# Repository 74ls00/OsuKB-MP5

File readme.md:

# Клавиатура для OSU!

Проект на базе клавиатуры v2 от noodlefighter, использованы кнопки МП9Р-1

.

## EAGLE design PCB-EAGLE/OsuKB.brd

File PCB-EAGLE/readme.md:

doc/ схема и плата в png.

OsuKB.sch OsuKB.brd плата схема и библиотека в формате eagle.

ExportGerber.cam задание экспорта в gerber/ .

SL6Import.lay6 плата импортированая в Sprint Layout 6.0 из gerber .

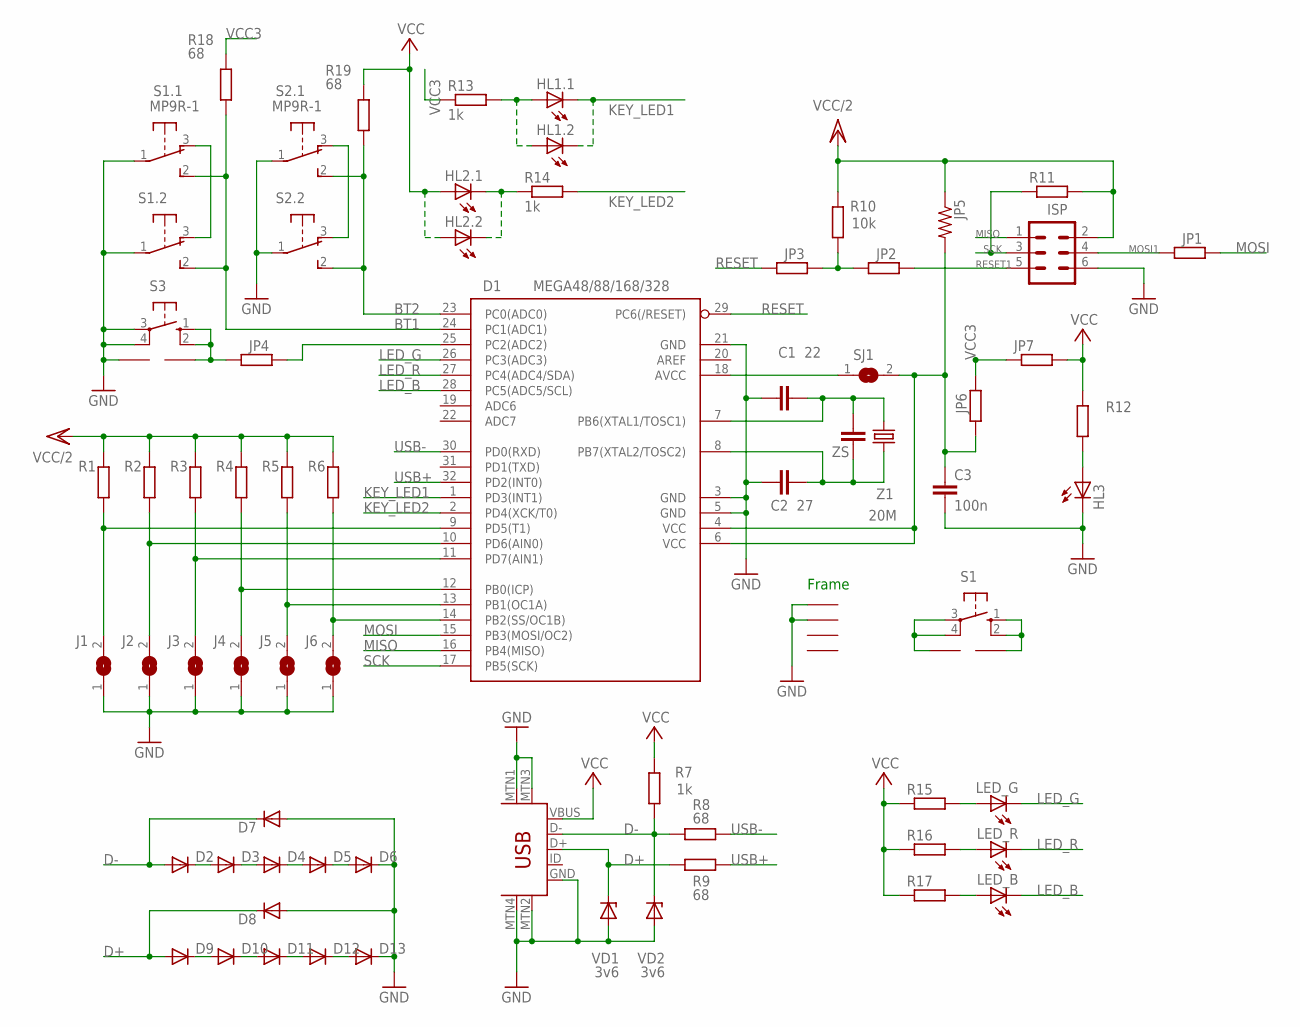
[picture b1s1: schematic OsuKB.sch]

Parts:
C1: 22; C0805
C2: 27; C0805
C3: 100n; C0805
D1: MEGA48/88/168/328; TQFP32-08
D2, D3, D4, D5, D6, D7, D8, D9, D10, D11, D12, D13: DIODE-SOD80C; SOD80C
GND: KB2
HL1.1, HL1.2, HL2.1, HL2.2: LEDSQR2X5; LED2X5
HL3: LEDSML0805; SML0805
ISP: MA03-2
J1, J2, J3, J4, J5, J6: SJ
JP1, JP2, JP3, JP4, JP6, JP7: R-EU_R1206W; R1206W
JP5: RESISTOR0805-RES; 0805
LED_B: LEDKA-3528ASYC; KA-3528ASYC
LED_G: LEDKA-3528ASYC; KA-3528ASYC
LED_R: LEDKA-3528ASYC; KA-3528ASYC
R1, R2, R3, R4, R5: R-EU_R1206W; R1206W
R6, R12, R15, R16, R17: R-EU_R0805; R0805
R7: 1k; R0805
R8, R9, R18, R19: 68; R0805
R10: 10k; R1206W
R11: R-EU_R0402; R0402
R13: 1k; R1206W
R14: 1k; 0207/12
S1: 10-XX; B3F-10XX; MPN B3F-1000
S1.1, S2.1: MP9R-1; MP5
S1.2, S2.2: MP5
S3: 10-XX; B3F-10XX
SJ1: SJ
U$1, U$6: PROGRAMMER_5.08; PROGRAMMER_KEY
VD1, VD2: 3v6; DO34Z7
X1: USB-MINIB-5PIN; USB-MINIB
Z1: 20M; HC49/S
ZS: C-EUC1812K; C1812K

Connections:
AVCC: D1.18 (AVCC), SJ1.1
BT1: D1.24 (PC1(ADC1)), R18.1, S1.1.2, S1.2.2
BT2: D1.23 (PC0(ADC0)), R19.1, S2.1.2, S2.2.2
BT3: D1.25 (PC2(ADC2)), JP4.1
D+: D8.C, D9.A, R9.1, VD1.C, X1.D+
D-: D2.A, D7.C, R7.1, R8.1, VD2.C, X1.D-
GND: C1.1, C2.1, C3.2, D1.3 (GND), D1.5 (GND), D1.21 (GND), D6.C, D7.A, D8.A, D13.C, GND.P$1 (1), GND.P$2 (2), HL3.C, ISP.6, J1.1, J2.1, J3.1, J4.1, J5.1, J6.1, S1.1.1, S1.2.1, S2.1.1, S2.2.1, S3.3, S3.4 (P1), U$6.P$1, VD1.A, VD2.A, X1.GND, X1.MTN1 (MTN2), X1.MTN2 (MTN3), X1.MTN3 (MTN1), X1.MTN4
KEY_LED1: D1.1 (PD3(INT1)), HL1.1.K (C), HL1.2.K (C)
KEY_LED2: D1.2 (PD4(XCK/T0)), R14.2
KEY_LED2.1: HL2.1.K (C), HL2.2.K (C), R14.1
LED_B: D1.28 (PC5(ADC5/SCL)), LED_B.C
LED_G: D1.26 (PC3(ADC3)), LED_G.C
LED_R: D1.27 (PC4(ADC4/SDA)), LED_R.C
MISO: D1.16 (PB4(MISO)), ISP.1
MOSI: D1.15 (PB3(MOSI/OC2)), JP1.1
MOSI1: ISP.4, JP1.2
unnamed: LED_G.A, R15.2
unnamed: D2.C, D3.A
unnamed: D3.C, D4.A
unnamed: D1.13 (PB1(OC1A)), J5.2, R5.1
unnamed: D1.14 (PB2(SS/OC1B)), J6.2, R6.1
unnamed: D1.10 (PD6(AIN0)), J2.2, R2.1
unnamed: D1.9 (PD5(T1)), J1.2, R1.1
unnamed: S1.1.3, S1.2.3
unnamed: D1.11 (PD7(AIN1)), J3.2, R3.1
unnamed: D1.12 (PB0(ICP)), J4.2, R4.1
unnamed: HL1.1.A, HL1.2.A, R13.2
unnamed: C1.2, D1.7 (PB6(XTAL1/TOSC1)), Z1.1, ZS.1
unnamed: C2.2, D1.8 (PB7(XTAL2/TOSC2)), Z1.2, ZS.2
unnamed: D4.C, D5.A
unnamed: HL3.A, R12.1
unnamed: S2.1.3, S2.2.3
unnamed: LED_R.A, R16.2
unnamed: LED_B.A, R17.2
unnamed: D5.C, D6.A
unnamed: D9.C, D10.A
unnamed: JP2.2, JP3.1, R10.1
unnamed: D10.C, D11.A
unnamed: D11.C, D12.A
unnamed: D12.C, D13.A
unnamed: C3.1, D1.4 (VCC), D1.6 (VCC), JP5.2, JP6.2, SJ1.2
unnamed: S1.3, S1.4 (P1), U$1.P$1
unnamed: S1.1 (S), S1.2 (S1), U$1.P$2
RESET: D1.29 (PC6(/RESET)), JP3.2
RESET1: ISP.5, JP2.1
S3: JP4.2, S3.1 (S), S3.2 (S1), U$6.P$2
SCK: D1.17 (PB5(SCK)), ISP.3, R11.1
USB+: D1.32 (PD2(INT0)), R9.2
USB-: D1.30 (PD0(RXD)), R8.2
VCC: HL2.1.A, HL2.2.A, JP7.2, R7.2, R12.2, R15.1, R16.1, R17.1, R19.2, X1.VBUS
VCC3: JP6.1, JP7.1, R13.1, R18.2
VCC/2: ISP.2, JP5.1, R1.2, R2.2, R3.2, R4.2, R5.2, R6.2, R10.2, R11.2

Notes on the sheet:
Frame

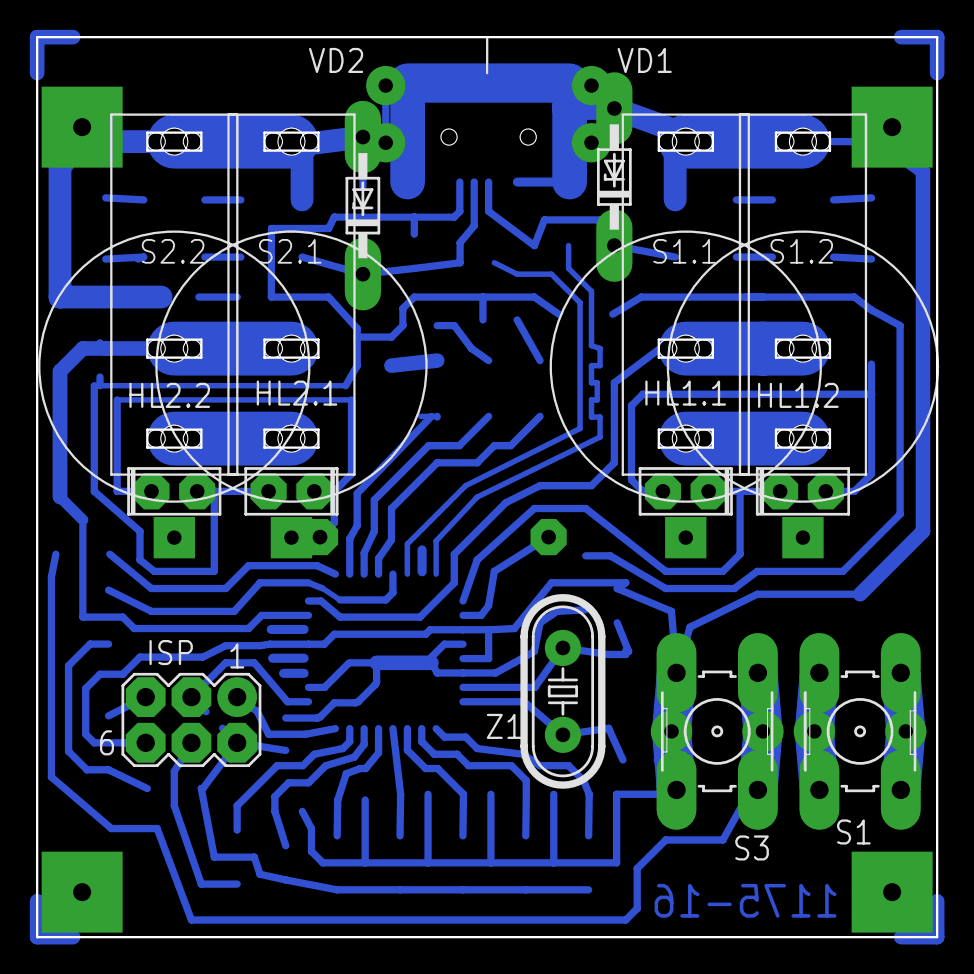
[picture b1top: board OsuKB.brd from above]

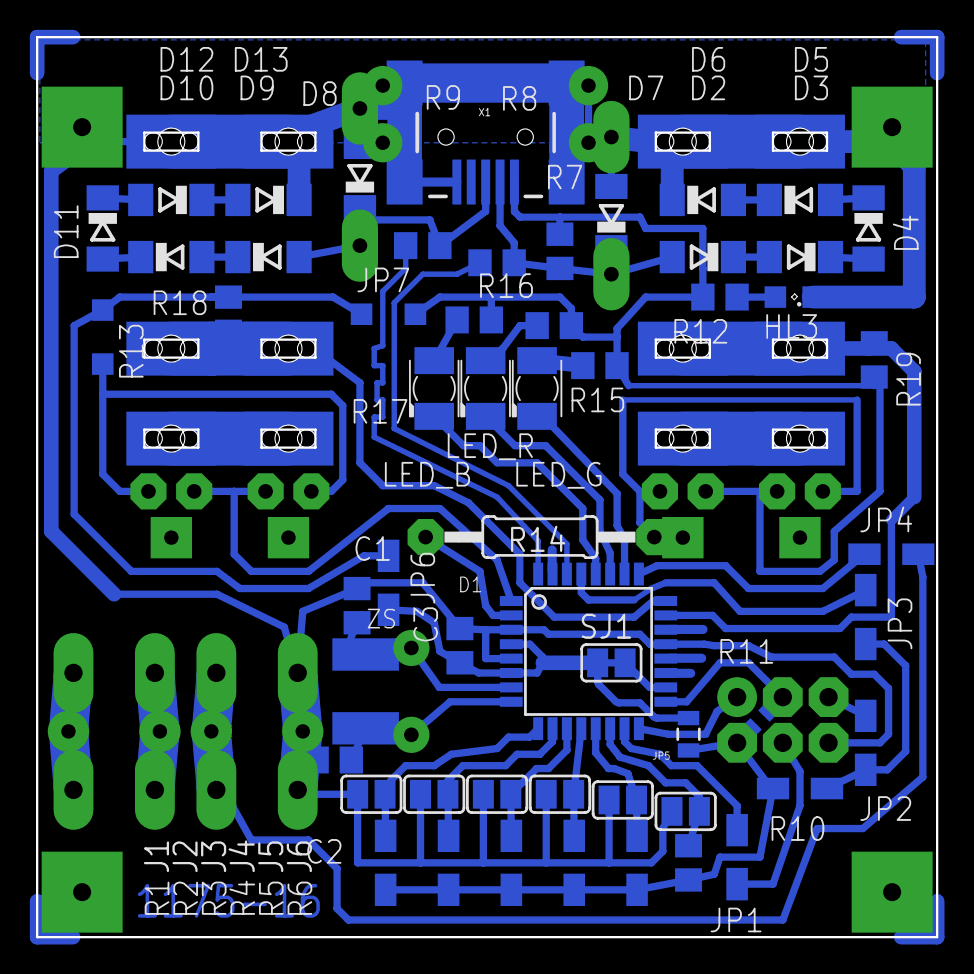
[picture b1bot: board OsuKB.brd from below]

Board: 2 copper layers, 50.0 x 50.0 mm, 72 parts (55 on the bottom side), 52 nets.

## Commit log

2016-05-04 b001
2016-05-04 b002
2016-05-05 b003
2016-05-27 r001
2016-05-27 r002
2016-05-27 r003
2016-05-27 r004
2016-05-27 r005
2016-07-19 move esc
2016-07-19 ed sh na
2016-07-20 save as assemble_chs_eng.odt
2016-07-29 +pic

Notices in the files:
parts and their libraries:
SparkFun-Connectors: Licensing: Creative Commons ShareAlike 4.0 International - https://creativecommons.org/licenses/by-sa/4.0
